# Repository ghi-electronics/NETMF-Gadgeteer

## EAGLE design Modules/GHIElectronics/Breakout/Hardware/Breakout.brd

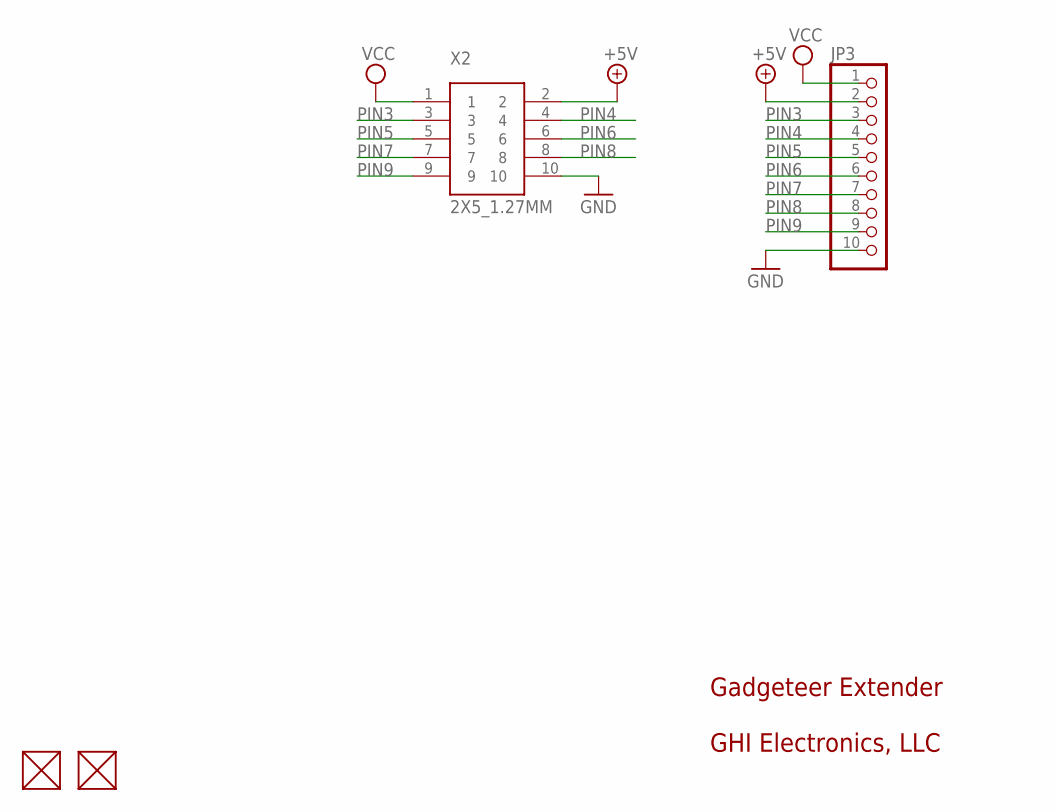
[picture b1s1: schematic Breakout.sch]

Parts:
FUD1, FUD2: FIDUCIAL; FIDUCIAL_40MIL
JP3: PINHD-1X10; 1X10
X2: 2X5_1.27MM

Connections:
+5V: JP3.2, X2.2
GND: JP3.10, X2.10
PIN3: JP3.3, X2.3
PIN4: JP3.4, X2.4
PIN5: JP3.5, X2.5
PIN6: JP3.6, X2.6
PIN7: JP3.7, X2.7
PIN8: JP3.8, X2.8
PIN9: JP3.9, X2.9
VCC: JP3.1, X2.1

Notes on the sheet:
Gadgeteer Extender
GHI Electronics, LLC

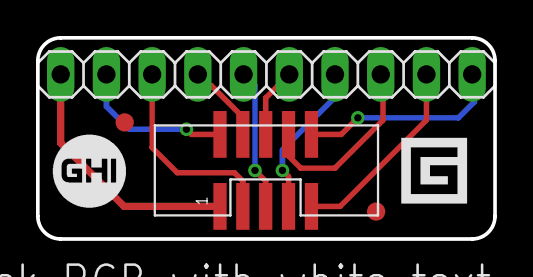
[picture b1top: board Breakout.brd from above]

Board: 2 copper layers, 25.4 x 11.2 mm, 4 parts (0 on the bottom side), 10 nets.

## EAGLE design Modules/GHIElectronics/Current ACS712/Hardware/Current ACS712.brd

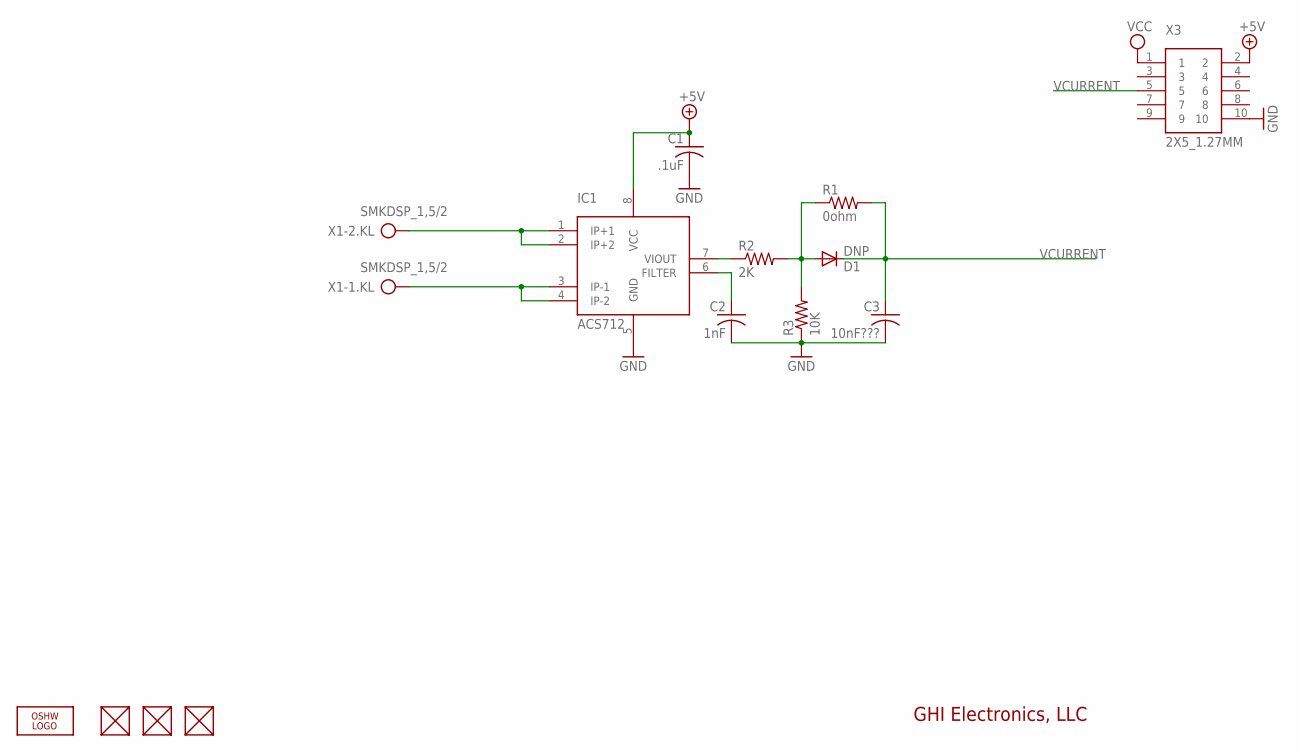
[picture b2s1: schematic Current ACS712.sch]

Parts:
C1: .1uF; C0603K
C2: 1nF; C0603K
C3: 10nF???; C0603K
D1: DNP; SOD323-W
FUD1, FUD2, FUD3: FIDUCIAL; FIDUCIAL_40MIL
IC1: ACS712; SO8
LOGO2: LOGO-OSHW-FILLX0200-NT; OSHW_FILLX200_NOTEXT
R1: 0ohm; R0603
R2: 2K; R0603
R3: 10K; R0603
X1: SMKDSP_1,5/2
X3: 2X5_1.27MM

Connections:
+5V: C1.1, IC1.8 (VCC), X3.2
GND: C1.2, C2.2, C3.2, IC1.5 (GND), R3.1, X3.10
unnamed: IC1.1 (IP+1), IC1.2 (IP+2), X1.2
unnamed: IC1.3 (IP-1), IC1.4 (IP-2), X1.1
unnamed: IC1.7 (VIOUT), R2.1
unnamed: D1.A, R1.1, R2.2, R3.2
unnamed: C2.1, IC1.6 (FILTER)
VCC: X3.1
VCURRENT: C3.1, D1.C, R1.2, X3.5

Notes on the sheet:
GHI Electronics, LLC

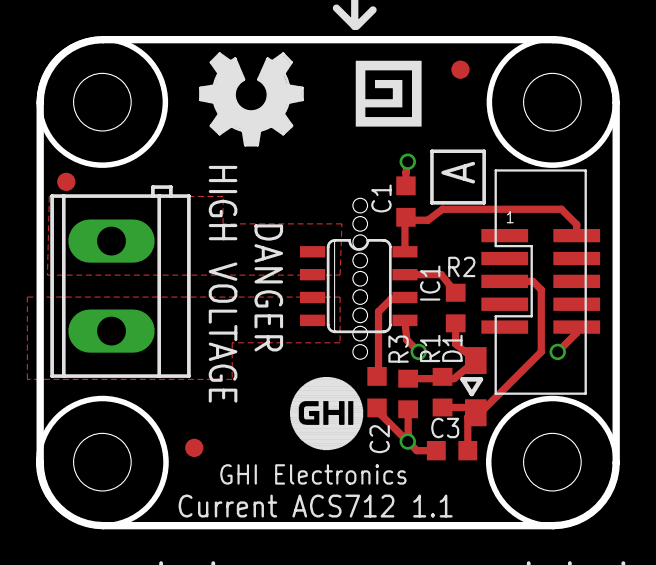
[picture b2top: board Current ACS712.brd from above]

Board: 2 copper layers, 32.0 x 27.0 mm, 14 parts (0 on the bottom side), 8 nets.

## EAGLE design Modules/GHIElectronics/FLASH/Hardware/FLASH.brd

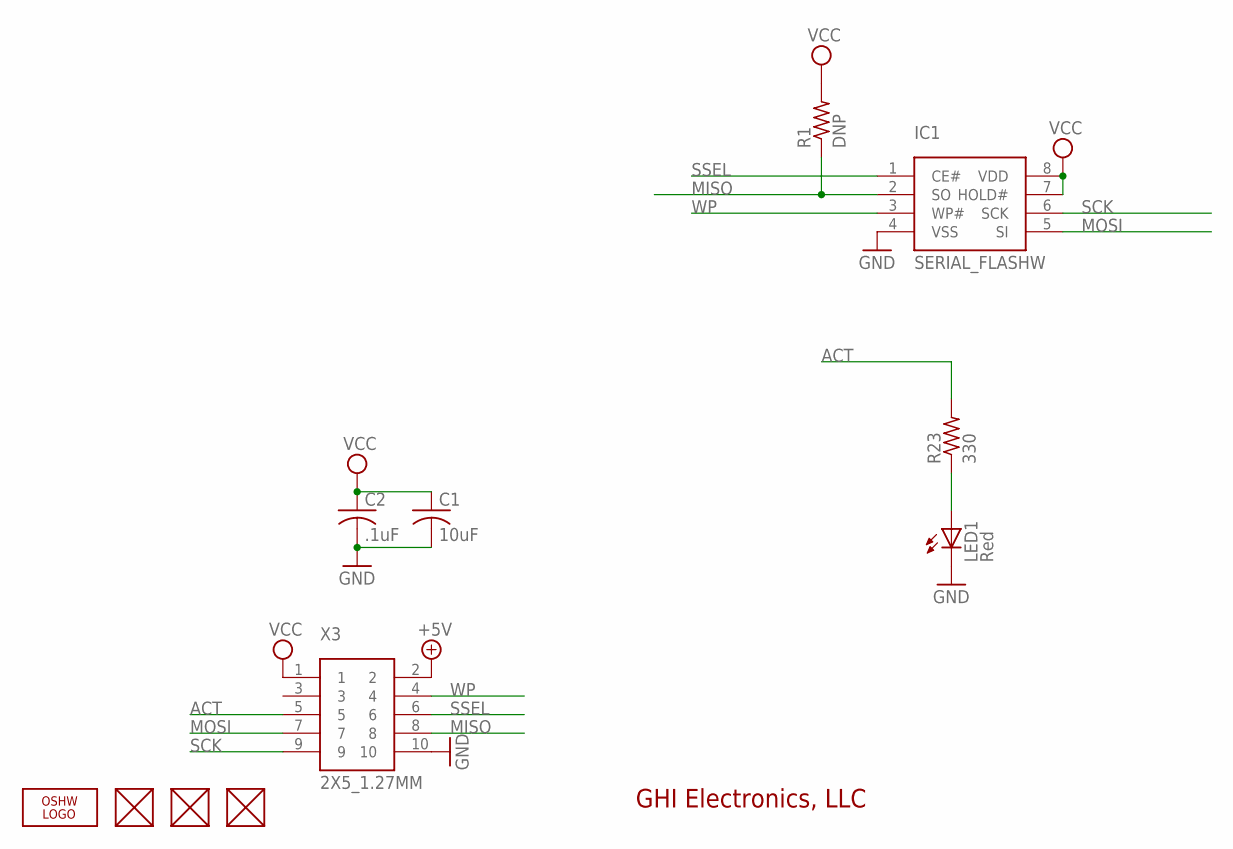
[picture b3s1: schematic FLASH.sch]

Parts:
C1: 10uF; C0805K
C2: .1uF; C0603K
FUD1, FUD2, FUD3: FIDUCIAL; FIDUCIAL_40MIL
IC1: SERIAL_FLASHW; SO8-WIDE
LED1: Red; CHIPLED_0805
LOGO: LOGO-OSHW-FILLX0200-NT; OSHW_FILLX200_NOTEXT
R1: DNP; R0402
R23: 330; R0603
X3: 2X5_1.27MM

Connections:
+5V: X3.2
ACT: R23.2, X3.5
GND: C1.2, C2.2, IC1.4 (VSS), LED1.C, X3.10
MISO: IC1.2 (SO), R1.1, X3.8
MOSI: IC1.5 (SI), X3.7
unnamed: LED1.A, R23.1
SCK: IC1.6 (SCK), X3.9
SSEL: IC1.1 (CE#), X3.6
VCC: C1.1, C2.1, IC1.7 (HOLD#), IC1.8 (VDD), R1.2, X3.1
WP: IC1.3 (WP#), X3.4

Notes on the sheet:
GHI Electronics, LLC

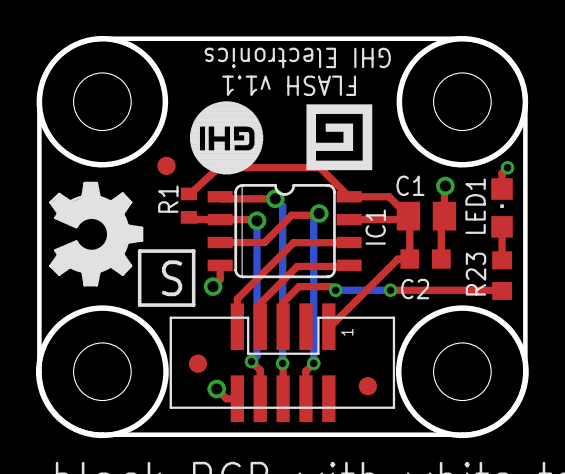
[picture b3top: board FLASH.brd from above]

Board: 2 copper layers, 27.0 x 22.0 mm, 11 parts (0 on the bottom side), 9 nets.

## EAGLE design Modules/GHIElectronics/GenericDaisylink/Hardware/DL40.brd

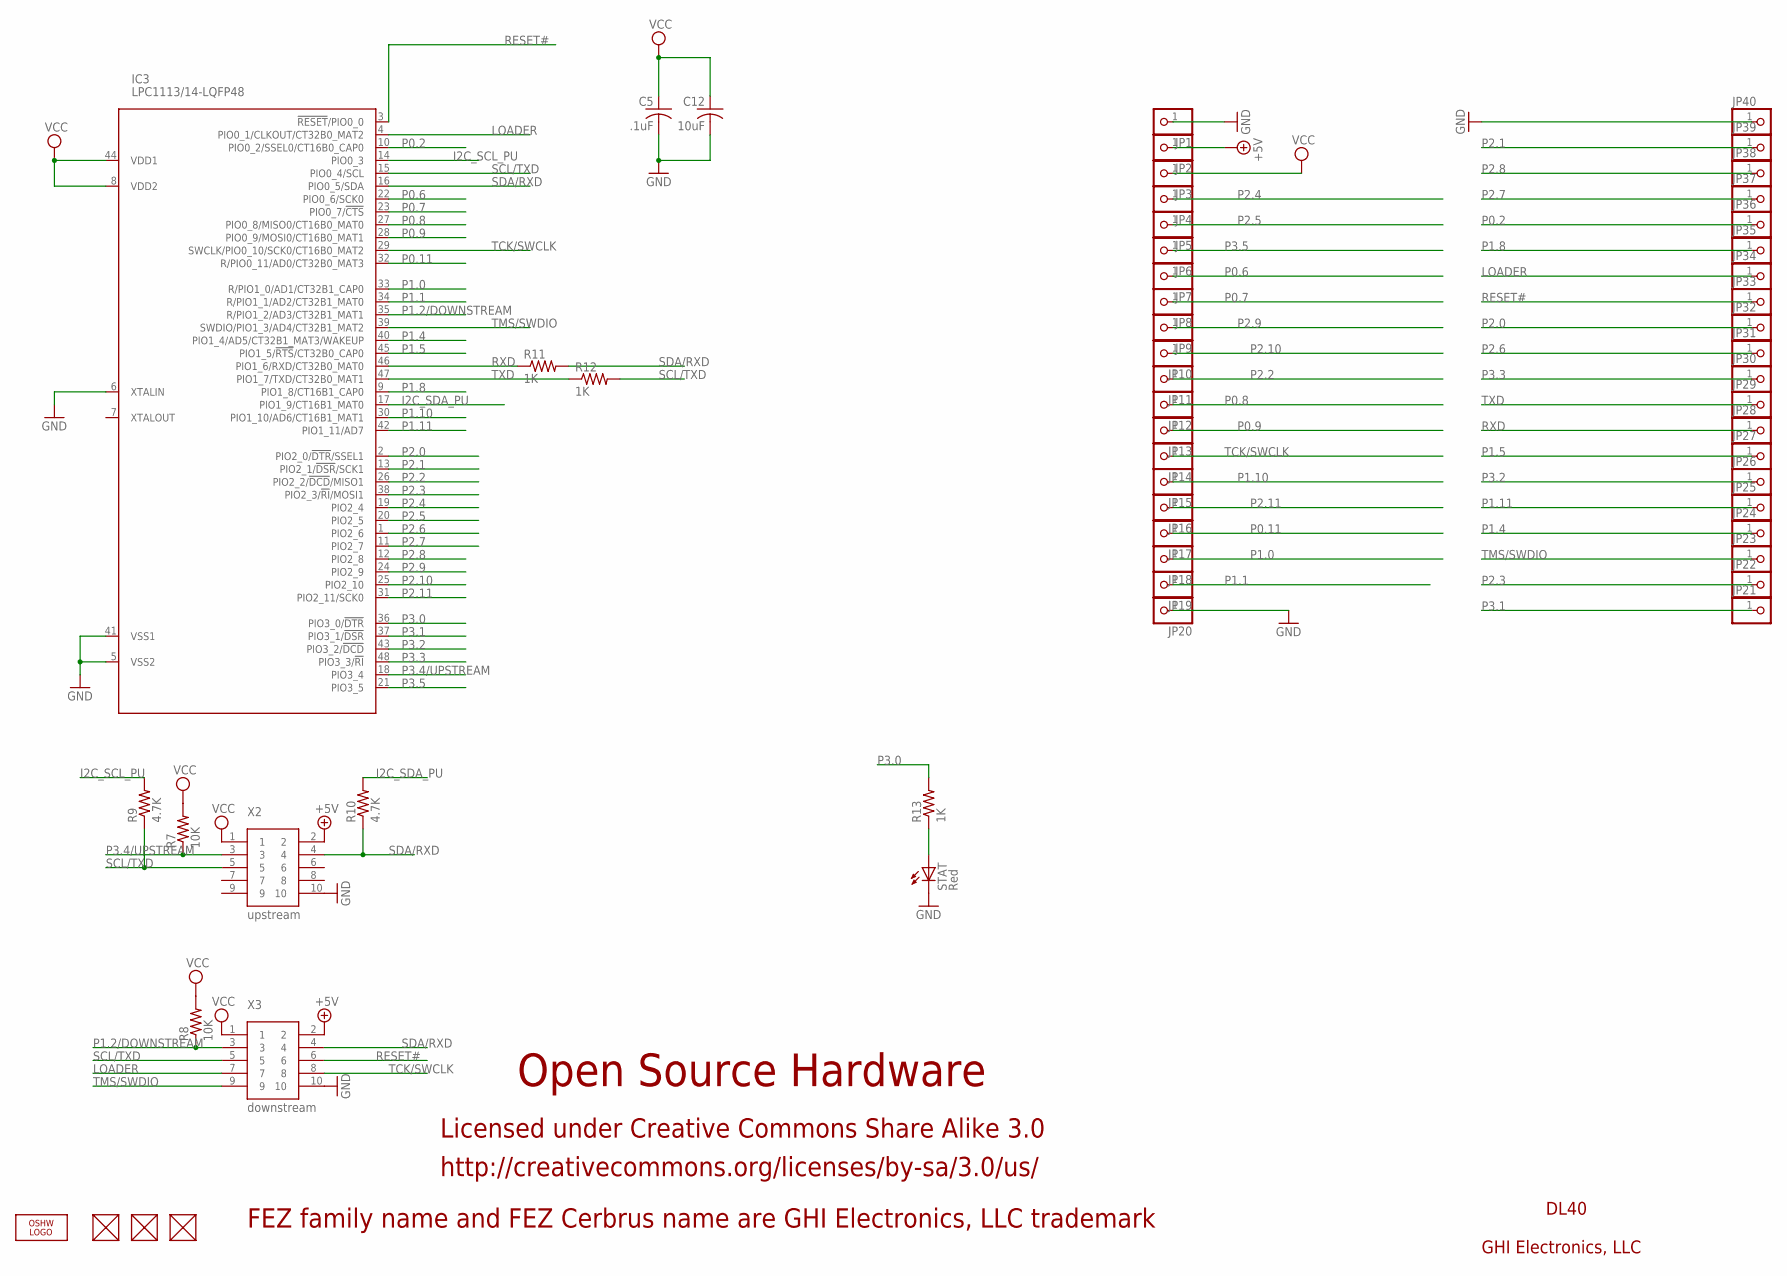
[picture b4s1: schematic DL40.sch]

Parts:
C5: .1uF; C0603K
C12: 10uF; C0805K
FUD4, FUD5, FUD6: FIDUCIAL; FIDUCIAL_40MIL
IC3: LPC1113/14-LQFP48; LQFP48
JP1, JP2, JP3, JP4, JP5, JP6, JP7, JP8, JP9, JP10, JP11, JP12, JP13, JP14, JP15, JP16, JP17, JP18, JP19, JP20, JP21, JP22, JP23, JP24, JP25, JP26, JP27, JP28, JP29, JP30, JP31, JP32, JP33, JP34, JP35, JP36, JP37, JP38, JP39, JP40: PINHD-1X1; 1X01
LOGO2: LOGO-OSHW-FILLX0200-NT; OSHW_FILLX200_NOTEXT
R7, R8: 10K; R0603
R9, R10: 4.7K; R0603
R11, R12, R13: 1K; R0603
STAT: Red; CHIPLED_0805
X2: upstream; 2X5_1.27MM
X3: downstream; 2X5_1.27MM

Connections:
+5V: JP2.1, X2.2, X3.2
GND: C5.2, C12.2, IC3.5 (VSS2), IC3.6 (XTALIN), IC3.41 (VSS1), JP1.1, JP20.1, JP40.1, STAT.C, X2.10, X3.10
I2C_SCL_PU: IC3.14 (PIO0_3), R9.2
I2C_SDA_PU: IC3.17 (PIO1_9/CT16B1_MAT0), R10.2
LOADER: IC3.4 (PIO0_1/CLKOUT/CT32B0_MAT2), JP34.1, X3.7
unnamed: R13.1, STAT.A
P0.2: IC3.10 (PIO0_2/SSEL0/CT16B0_CAP0), JP36.1
P0.6: IC3.22 (PIO0_6/SCK0), JP7.1
P0.7: IC3.23 (PIO0_7/!CTS!), JP8.1
P0.8: IC3.27 (PIO0_8/MISO0/CT16B0_MAT0), JP12.1
P0.9: IC3.28 (PIO0_9/MOSI0/CT16B0_MAT1), JP13.1
P0.11: IC3.32 (R/PIO0_11/AD0/CT32B0_MAT3), JP17.1
P1.0: IC3.33 (R/PIO1_0/AD1/CT32B1_CAP0), JP18.1
P1.1: IC3.34 (R/PIO1_1/AD2/CT32B1_MAT0), JP19.1
P1.2/DOWNSTREAM: IC3.35 (R/PIO1_2/AD3/CT32B1_MAT1), R8.1, X3.3
P1.4: IC3.40 (PIO1_4/AD5/CT32B1_MAT3/WAKEUP), JP24.1
P1.5: IC3.45 (PIO1_5/!RTS!/CT32B0_CAP0), JP27.1
P1.8: IC3.9 (PIO1_8/CT16B1_CAP0), JP35.1
P1.10: IC3.30 (PIO1_10/AD6/CT16B1_MAT1), JP15.1
P1.11: IC3.42 (PIO1_11/AD7), JP25.1
P2.0: IC3.2 (PIO2_0/!DTR!/SSEL1), JP32.1
P2.1: IC3.13 (PIO2_1/!DSR!/SCK1), JP39.1
P2.2: IC3.26 (PIO2_2/!DCD!/MISO1), JP11.1
P2.3: IC3.38 (PIO2_3/!RI!/MOSI1), JP22.1
P2.4: IC3.19 (PIO2_4), JP4.1
P2.5: IC3.20 (PIO2_5), JP5.1
P2.6: IC3.1 (PIO2_6), JP31.1
P2.7: IC3.11 (PIO2_7), JP37.1
P2.8: IC3.12 (PIO2_8), JP38.1
P2.9: IC3.24 (PIO2_9), JP9.1
P2.10: IC3.25 (PIO2_10), JP10.1
P2.11: IC3.31 (PIO2_11/SCK0), JP16.1
P3.0: IC3.36 (PIO3_0/!DTR!), R13.2
P3.1: IC3.37 (PIO3_1/!DSR!), JP21.1
P3.2: IC3.43 (PIO3_2/!DCD!), JP26.1
P3.3: IC3.48 (PIO3_3/!RI!), JP30.1
P3.4/UPSTREAM: IC3.18 (PIO3_4), R7.1, X2.3
P3.5: IC3.21 (PIO3_5), JP6.1
RESET#: IC3.3 (!RESET!/PIO0_0), JP33.1, X3.6
RXD: IC3.46 (PIO1_6/RXD/CT32B0_MAT0), JP28.1, R11.1
SCL/TXD: IC3.15 (PIO0_4/SCL), R9.1, R12.2, X2.5, X3.5
SDA/RXD: IC3.16 (PIO0_5/SDA), R10.1, R11.2, X2.4, X3.4
TCK/SWCLK: IC3.29 (SWCLK/PIO0_10/SCK0/CT16B0_MAT2), JP14.1, X3.8
TMS/SWDIO: IC3.39 (SWDIO/PIO1_3/AD4/CT32B1_MAT2), JP23.1, X3.9
TXD: IC3.47 (PIO1_7/TXD/CT32B0_MAT1), JP29.1, R12.1
VCC: C5.1, C12.1, IC3.8 (VDD2), IC3.44 (VDD1), JP3.1, R7.2, R8.2, X2.1, X3.1

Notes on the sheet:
DL40
GHI Electronics, LLC
Open Source Hardware
Licensed under Creative Commons Share Alike 3.0
FEZ family name and FEZ Cerbrus name are GHI Electronics, LLC trademark
http://creativecommons.org/licenses/by-sa/3.0/us/

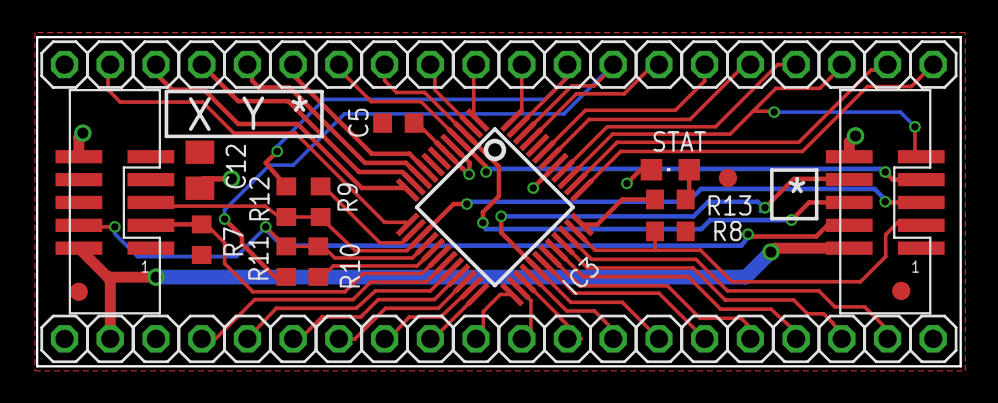
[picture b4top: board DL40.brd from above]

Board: 2 copper layers, 51.3 x 18.3 mm, 57 parts (1 on the bottom side), 46 nets.
